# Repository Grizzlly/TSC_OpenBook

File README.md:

# OpenBook

An open source e-book reader based on ESP32.

## Block diagram

## Hardware features

The main component of the device is the `ESP32` microcontroller, which is responsible for all the processing and control of the device. The `ESP32` is a powerful microcontroller with built-in Wi-Fi and Bluetooth capabilities, making it ideal for IoT applications.

Apart from the microcontroller, we have:

- `E-Paper Display`: connected via SPI interface.
- `SD Card`: connected via SPI interface.
- `USB-C charging and protection`: connected to the battery and the microcontroller. It also has electro static discharge protection.
- `Environmental sensors`: connected via I2C interface. These sensors measure temperature, humidity, and pressure.

## Power consumption

The `ESP32` microcontroller consumes `~250 mA` when
in use.
The display uses `~15 mA` when active.
The environmental sensors use `~3 mA` when active.

In total when active, the device consumes `~270 mA`. Given
that the battery has a capacity of `1800 mAh`,
we should expect a battery life of `~6.5 hours` of continuous use.

## Pin mapping for the ESP32

| Pin Name | Description |                                                               
| -------- | ----------- |
| EN       | Reset |
| IO0      | Interrupt RTC |
| IO1      | Oscilator RTC |
| IO2      | SPI MISO |
| IO3      | Status display |
| IO4      | SD Card |
| IO5      | Data/Command |
| IO6      | SPI clock |
| IO7      | SPI data out |
| IO9      | Boot |
| IO10     | SPI E-Paper display command |
| IO11     | EPD |
| IO12     | Flash |
| IO13     | USB Data - |
| IO14     | USB Data + |
| IO15     | Navigation |
| IO16     | TX |
| IO17     | RX |
| IO18     | Reset DS3231 |
| IO19     | I2C Power |
| IO20     | EPD Power |
| IO21     | BME688 |
| IO22     | BME688 |
| IO23     | Reset display |

## BOM

| Piece Name                  | Quantity | Link                                                                                                                                                                                                               |
| --------------------------- | -------- | ------------------------------------------------------------------------------------------------------------------------------------------------------------------------------------------------------------------ |
| ADAFRUIT_LEDCHIP-LED0603    | 1        | https://www.snapeda.com/parts/KP-1608SURCK/Kingbright/view-part/?ref=search&t=LED%200603                                                                                                                           |
| C0402                       | 1        | https://componentsearchengine.com/part-view/CC0402MRX5R5BB106/YAGEO                                                                                                                                                |
| 112ATAARR03                 | 1        | https://www.snapeda.com/parts/112A-TAAR-R03/Attend/view-part/                                                                                                                                                      |
| 744043680                   | 1        | https://eu.mouser.com/ProductDetail/Wurth-Elektronik/744043680?qs=PGXP4M47uW6VkZq%252BkzjrHA%3D%3D                                                                                                                 |
| BD5229G-TR                  | 1        | https://www.snapeda.com/parts/BD5229G-TR/Rohm/view-part/?ref=search&t=BD5229G-TR                                                                                                                                   |
| CPH3225A                    | 1        | https://www.snapeda.com/parts/CPH3225A/Seiko/view-part/                                                                                                                                                            |
| BUTTON_CUSYOMV1             | 3        | https://www.snapeda.com/search/?q=EVQP7L01P&search-type=parts                                                                                                                                                      |
| DS3231SN                    | 1        | https://www.snapeda.com/parts/DS3231SN%23/Analog%20Devices/view-part/?ref=search&t=DS3231SN%23                                                                                                                     |
| ESP32                       | 1        | https://www.snapeda.com/parts/ESP32-C6-WROOM-1-N8/Espressif%20Systems/view-part/?ref=search&t=ESP32-C6-WROOM-1-N8                                                                                                  |
| VARISTOR                    | 1        | https://ro.mouser.com/ProductDetail/EPCOS-TDK/B72520T0350K062?qs=dEfas%2FXlABIszF52uu7vrg%3D%3D                                                                                                                    |
| SD0805S020S1R0              | 1        | https://componentsearchengine.com/part-view/SD0805S020S1R0/Kyocera%20AVX                                                                                                                                           |
| BME680                      | 1        | https://www.snapeda.com/parts/BME680/Bosch%20Sensortec/view-part/?ref=search&t=bme680                                                                                                                              |
| R0402                       | 1        | https://componentsearchengine.com/part-view/R0402%201%25%20100%20K%20(RC0402FR-07100KL)/YAGEO                                                                                                                      |
| MOSFET                      | 1        | https://componentsearchengine.com/part-view/DMG2305UX-7/Diodes%20Incorporated                                                                                                                                      |
| MCP73831                    | 1        | https://componentsearchengine.com/part-view/MCP73831T-2ACI%2FOT/Microchip                                                                                                                                          |
| SRJ                         | 1        | https://componentsearchengine.com/part-view/FH34SRJ-24S-0.5SH(99)/Hirose                                                                                                                                           |
| MBR0530                     | 1        | https://www.snapeda.com/parts/MBR0530/Onsemi/view-part/                                                                                                                                                            |
| PGB1010603MR                | 1        | https://www.snapeda.com/parts/PGB1010603MR/Littelfuse/view-part/                                                                                                                                                   |
| QWIIC_CONNECTOR             | 1        | https://www.snapeda.com/parts/PRT-14417/SparkFun/view-part/                                                                                                                                                        |
| RCL_CPOL-EU                 | 1        | https://grabcad.com/library/tantalum-smd-capacitor-type-b-3528-1                                                                                                                                                   |
| SAMACSYS_PARTS_USB4110-GF-A | 1        | https://www.snapeda.com/parts/USB4110-GF-A./Global%20Connector%20Technology/view-part/                                                                                                                             |
| SI1308EDL-T1-GE3            | 1        | https://www.snapeda.com/parts/SI1308EDL-T1-GE3/Vishay/view-part/                                                                                                                                                   |
| USBLC6-2SC6Y                | 1        | https://www.snapeda.com/parts/USBLC6-2SC6Y/STMicroelectronics/view-part/?ref=dk&t=USBLC6-2SC6Y&con_ref=None                                                                                                        |
| W25Q512JVEIQ                | 1        | https://www.snapeda.com/parts/W25Q512JVEIQ/Winbond%20Electronics/view-part/?ref=search&t=W25Q512JVEIQ                                                                                                              |
| XC6220A331MR-G              | 1        | https://ro.mouser.com/ProductDetail/Torex-Semiconductor/XC6220A331MR-G?qs=AsjdqWjXhJ8ZSWznL1J0gg%3D%3D&utm_source=octopart&utm_medium=aggregator&utm_campaign=865-XC6220A331MR-G&utm_content=Torex%20Semiconductor |

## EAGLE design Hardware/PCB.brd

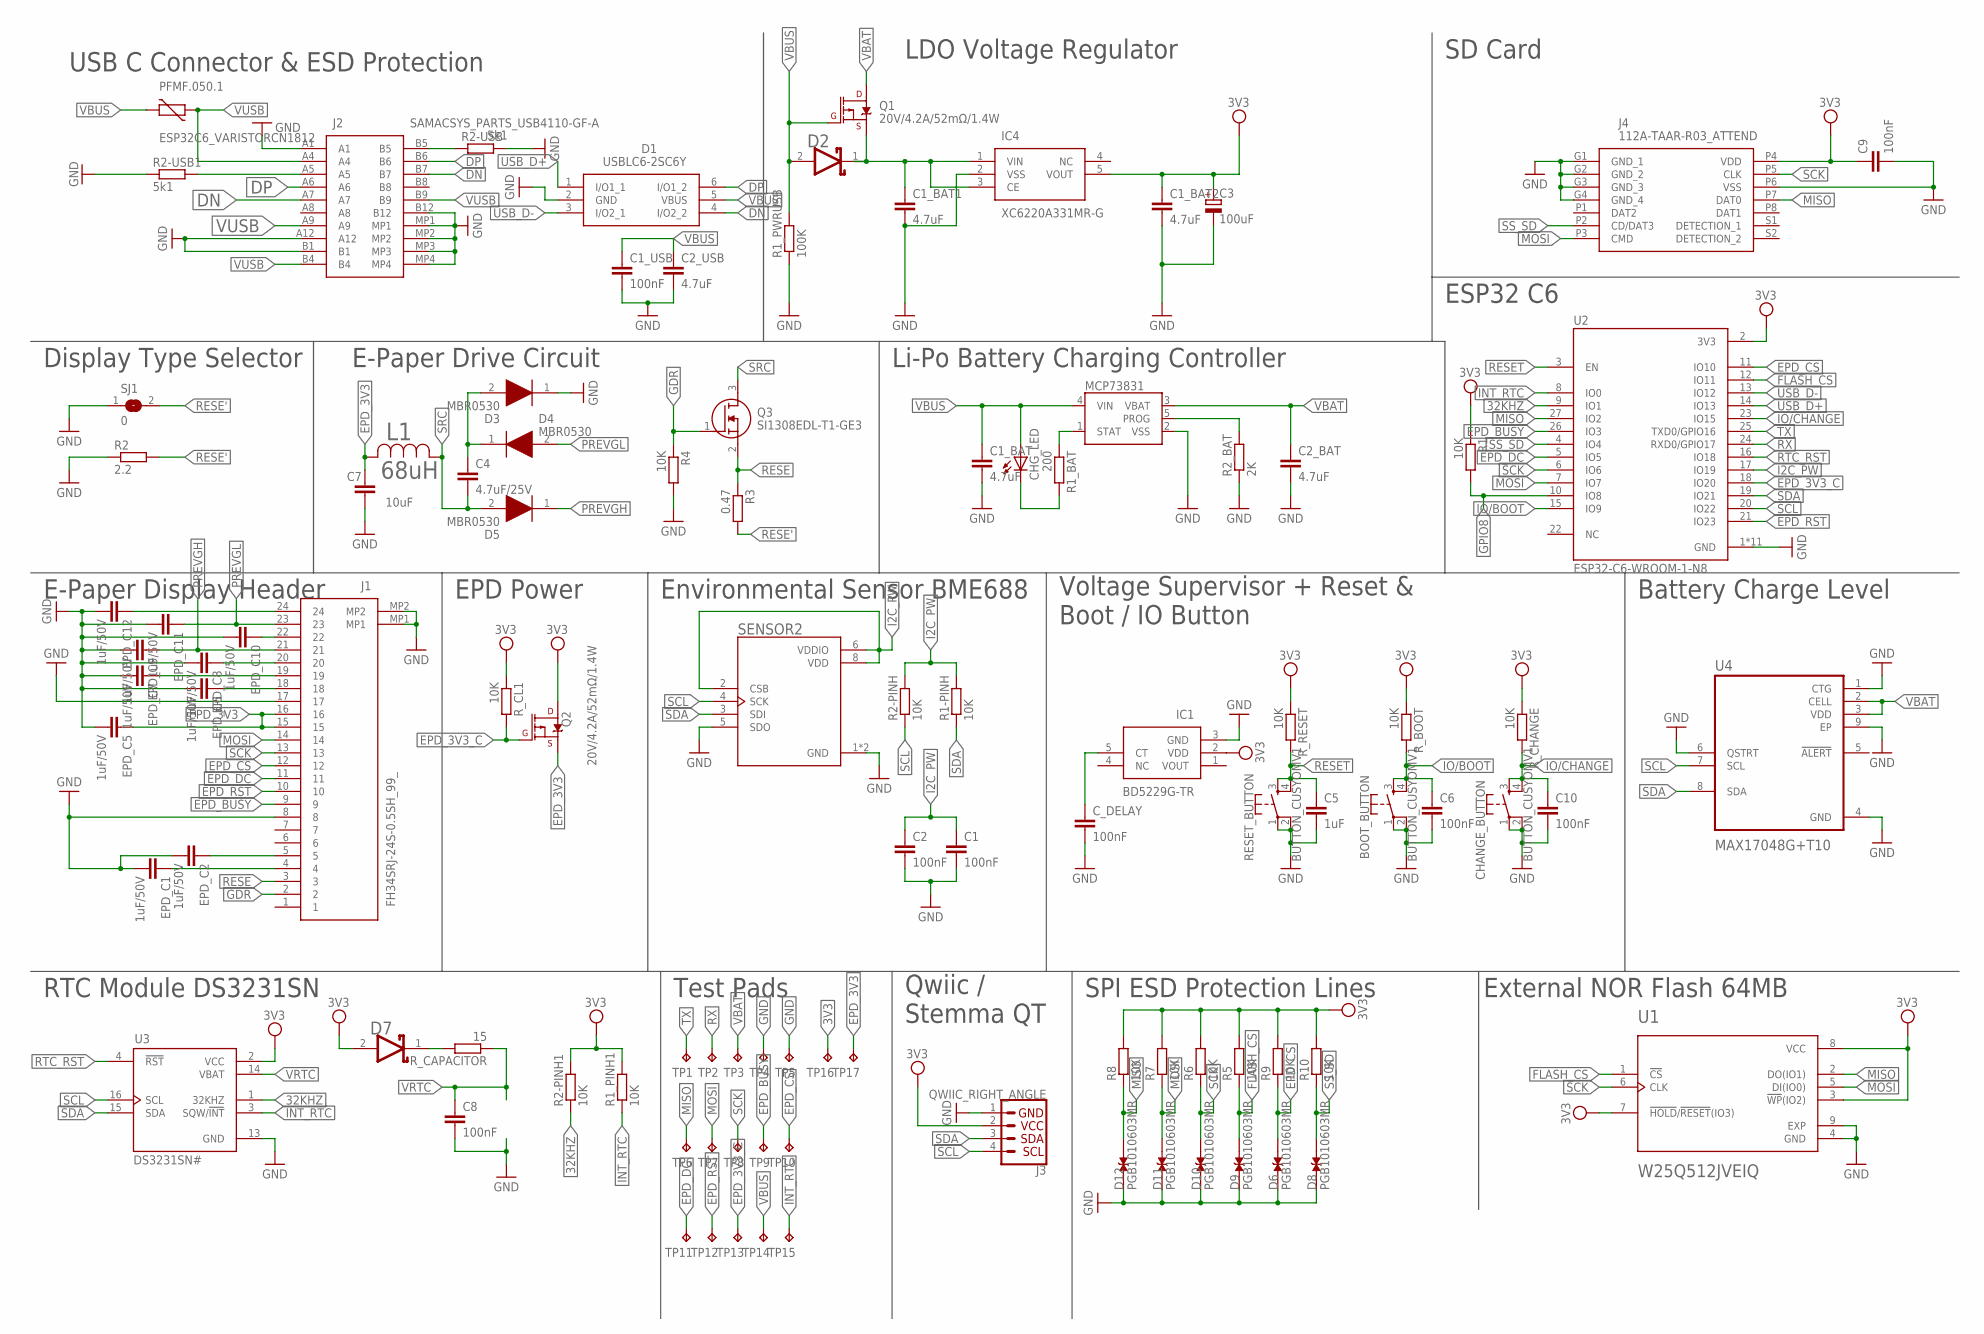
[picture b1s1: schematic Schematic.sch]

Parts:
BOOT_BUTTON: BUTTON_CUSYOMV1; MYBUTTON
C1, C1_USB, C2, C6, C8, C9, C10: 100nF; ESP32_WROVER_EAGLE-LTSPICE_C0402
C1_BAT, C1_BAT1, C1_BAT2, C2_BAT, C2_USB: 4.7uF; ESP32_WROVER_EAGLE-LTSPICE_C0402
C3: 100uF; RCL_CT3528
C4: 4.7uF/25V; ESP32_WROVER_EAGLE-LTSPICE_C0402
C5: 1uF; ESP32_WROVER_EAGLE-LTSPICE_C0402
C7: 10uF; ESP32_WROVER_EAGLE-LTSPICE_C0402
CHANGE_BUTTON: BUTTON_CUSYOMV1; MYBUTTON
CHG_LED: ADAFRUIT_LEDCHIP-LED0603; ADAFRUIT_CHIP-LED0603
C_DELAY: 100nF; ESP32_WROVER_EAGLE-LTSPICE_C0402
D1: USBLC6-2SC6Y; SOT95P280X145-6N
D2, D7: ESP32_WROVER_AVX---SD0805S020S1R0_AVX_SD0805S020S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; ESP32_WROVER_AVX---SD0805S020S1R0_AVX_SD0805S020S1R0_0
D3, D4, D5: MBR0530; SOD3716X135N
D6, D8, D9, D10, D11, D12: PGB1010603MR; DIOC1608X36N
EPD_C1, EPD_C2, EPD_C5, EPD_C6, EPD_C7, EPD_C8, EPD_C9, EPD_C10, EPD_C11, EPD_C12: 1uF/50V; ESP32_WROVER_EAGLE-LTSPICE_C0402
IC1: BD5229G-TR; SOT95P280X125-5N
IC4: XC6220A331MR-G; SOT95P280X120-5N
J1: FH34SRJ-24S-0.5SH_99_; FH34SRJ24S05SH99
J2: SAMACSYS_PARTS_USB4110-GF-A; SAMACSYS_PARTS_USB4110GFA
J3: QWIIC_RIGHT_ANGLE; JST04_1MM_RA
J4: 112A-TAAR-R03_ATTEND; 112ATAARR03ATTEND
L1: 68uH; IND_4828-WE-TPC_WRE
MCP73831: ESP32_WROVER_SPARKFUN-IC-POWER_MCP73831; ESP32_WROVER_SPARKFUN-IC-POWER_SOT23-5
PFMF.050.1: ESP32C6_VARISTORCN1812; ESP32C6_VARISTOR_CT/CN1812
Q1, Q2: 20V/4.2A/52mΩ/1.4W; ESP32_WROVER_SPARKFUN-DISCRETESEMI_SOT23-3
Q3: SI1308EDL-T1-GE3; SOT65P210X110-3N
R1, R1-PINH, R1_PINH1, R2-PINH, R2-PINH1, R4, R5, R6, R7, R8, R9, R10: 10K; ESP32_WROVER_EAGLE-LTSPICE_R0402
R1_BAT: 200; ESP32_WROVER_EAGLE-LTSPICE_R0402
R1_PWRUSB: 100K; ESP32_WROVER_EAGLE-LTSPICE_R0402
R2: 2.2; ESP32_WROVER_EAGLE-LTSPICE_R0402
R2-USB, R2-USB1: 5k1; ESP32_WROVER_EAGLE-LTSPICE_R0402
R2_BAT: 2K; ESP32_WROVER_EAGLE-LTSPICE_R0402
R3: 0.47; ESP32_WROVER_EAGLE-LTSPICE_R0402
RESET_BUTTON: BUTTON_CUSYOMV1; MYBUTTON
R_BOOT: 10K; ESP32_WROVER_EAGLE-LTSPICE_R0402
R_CAPACITOR: 15; ESP32_WROVER_EAGLE-LTSPICE_R0402
R_CHANGE: 10K; ESP32_WROVER_EAGLE-LTSPICE_R0402
R_CL1: 10K; ESP32_WROVER_EAGLE-LTSPICE_R0402
R_RESET: 10K; ESP32_WROVER_EAGLE-LTSPICE_R0402
SENSOR2: ESP32_WROVER_BME680_BME680; ESP32_WROVER_BME680_PSON80P300X300X100-8N
SJ1: 0; SJ
TP1, TP2, TP3, TP4, TP5, TP6, TP7, TP8, TP9, TP10, TP11, TP12, TP13, TP14, TP15, TP16, TP17: TPTP20R; TP20R
U1: W25Q512JVEIQ; SON127P600X800X80-9N
U2: ESP32-C6-WROOM-1-N8; XCVR_ESP32-C6-WROOM-1-N8
U3: DS3231SN#; SOIC127P1032X265-16N
U4: MAX17048G+T10; SON50P200X200X80-9N

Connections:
3V3: C1_BAT2.1, C3.+, C9.1, D7.2 (ANODE), IC1.2 (VDD), IC4.5 (VOUT), J3.2, J4.P4 (VDD), Q2.3 (D), R1.1, R1_PINH1.2, R2-PINH1.2, R5.2, R6.2, R7.2, R8.2, R9.2, R10.2, R_BOOT.1, R_CHANGE.1, R_CL1.1, R_RESET.1, TP16.TP, U1.3 (!WP!(IO2)), U1.7 (!HOLD!/!RESET!(IO3)), U1.8 (VCC), U2.2 (3V3), U3.2 (VCC)
32KHZ: R2-PINH1.1, U2.9 (IO1), U3.1 (32KHZ)
DN: D1.4 (I/O2_2), J2.A7, J2.B7
DP: D1.6 (I/O1_2), J2.A6, J2.B6
EPD_3V3: C7.1, EPD_C5.1, J1.15, J1.16, L1.2, Q2.2 (S), TP17.TP
EPD_3V3_C: Q2.1 (G), R_CL1.2, TP13.TP, U2.18 (IO20)
EPD_BUSY: J1.9, TP9.TP, U2.26 (IO3)
EPD_CS: D6.2, J1.12, R9.1, TP10.TP, U2.11 (IO10)
EPD_DC: J1.11, TP11.TP, U2.5 (IO5)
EPD_RST: J1.10, TP12.TP, U2.21 (IO23)
FLASH_CS: D9.2, R5.1, U1.1 (!CS), U2.12 (IO11)
GDR: J1.2, Q3.1 (G), R4.1
GND: BOOT_BUTTON.1, BOOT_BUTTON.2, C1.2, C1_BAT.2, C1_BAT1.2, C1_BAT2.2, C1_USB.2, C2.2, C2_BAT.2, C2_USB.2, C3.-, C5.2, C6.2, C7.2, C8.2, C9.2, C10.2, CHANGE_BUTTON.1, CHANGE_BUTTON.2, C_DELAY.2, D1.2 (GND), D3.1 (K), D6.1, D8.1, D9.1, D10.1, D11.1, D12.1, EPD_C1.2, EPD_C2.2, EPD_C5.2, EPD_C6.2, EPD_C7.2, EPD_C8.2, EPD_C9.2, EPD_C10.2, EPD_C11.2, EPD_C12.2, IC1.3 (GND), IC4.2 (VSS), J1.8, J1.17, J1.MP1, J1.MP2, J2.A1, J2.A12, J2.B1, J2.B12, J2.MP1, J2.MP2, J2.MP3, J2.MP4, J3.1, J4.G1 (GND_1), J4.G2 (GND_2), J4.G3 (GND_3), J4.G4 (GND_4), J4.P6 (VSS), MCP73831.2 (VSS), R1_PWRUSB.1, R2.1, R2-USB.2, R2-USB1.1, R2_BAT.1, R4.2, RESET_BUTTON.1, RESET_BUTTON.2, SENSOR2.1 (GND), SENSOR2.5 (SDO), SENSOR2.7 (GND), SJ1.1, TP4.TP, TP5.TP, U1.4 (GND), U1.9 (EXP), U2.1 (GND), U2.28 (GND), U2.29_1 (GND), U2.29_2 (GND), U2.29_3 (GND), U2.29_4 (GND), U2.29_5 (GND), U2.29_6 (GND), U2.29_7 (GND), U2.29_8 (GND), U2.29_9 (GND), U3.13 (GND), U4.1 (CTG), U4.4 (GND), U4.6 (QSTRT), U4.9 (EP)
GPIO8: R1.2, U2.10 (IO8)
I2C_PW: C1.1, C2.1, R1-PINH.2, R2-PINH.2, SENSOR2.2 (CSB), SENSOR2.6 (VDDIO), SENSOR2.8 (VDD), U2.17 (IO19)
INT_RTC: R1_PINH1.1, TP15.TP, U2.8 (IO0), U3.3 (SQW/!INT)
IO/BOOT: BOOT_BUTTON.3, BOOT_BUTTON.4, C6.1, R_BOOT.2, U2.15 (IO9)
IO/CHANGE: C10.1, CHANGE_BUTTON.3, CHANGE_BUTTON.4, R_CHANGE.2, U2.23 (IO15)
MISO: D12.2, J4.P7 (DAT0), R8.1, TP6.TP, U1.2 (DO(IO1)), U2.27 (IO2)
MOSI: D11.2, J1.14, J4.P3 (CMD), R7.1, TP7.TP, U1.5 (DI(IO0)), U2.7 (IO7)
unnamed: J2.A5, R2-USB1.2
unnamed: J2.B5, R2-USB.1
unnamed: C1_BAT1.1, D2.1 (CATHODE), IC4.1 (VIN), IC4.3 (CE), Q1.2 (S)
unnamed: C4.1, D3.2 (A), D4.1 (K)
unnamed: MCP73831.1 (STAT), R1_BAT.1
unnamed: CHG_LED.C, R1_BAT.2
unnamed: MCP73831.5 (PROG), R2_BAT.2
unnamed: EPD_C1.1, J1.4
unnamed: EPD_C2.1, J1.5
unnamed: EPD_C10.1, J1.22
unnamed: EPD_C8.1, J1.20
unnamed: EPD_C6.1, J1.18
unnamed: C_DELAY.1, IC1.5 (CT)
unnamed: EPD_C12.1, J1.24
unnamed: D7.1 (CATHODE), R_CAPACITOR.2
unnamed: EPD_C7.1, J1.19
PREVGH: D5.1 (K), EPD_C9.1, J1.21
PREVGL: D4.2 (A), EPD_C11.1, J1.23
RESE: J1.3, Q3.2 (S), R3.1
RESE': R2.2, R3.2, SJ1.2
RESET: C5.1, RESET_BUTTON.3, RESET_BUTTON.4, R_RESET.2, U2.3 (EN)
RTC_RST: U2.16 (IO18), U3.4 (!RST)
RX: TP2.TP, U2.24 (RXD0/GPIO17)
SCK: D10.2, J1.13, J4.P5 (CLK), R6.1, TP8.TP, U1.6 (CLK), U2.6 (IO6)
SCL: J3.4, R2-PINH.1, SENSOR2.4 (SCK), U2.20 (IO22), U3.16 (SCL), U4.7 (SCL)
SDA: J3.3, R1-PINH.1, SENSOR2.3 (SDI), U2.19 (IO21), U3.15 (SDA), U4.8 (SDA)
SRC: C4.2, D5.2 (A), L1.1, Q3.3 (D)
SS_SD: D8.2, J4.P2 (CD/DAT3), R10.1, U2.4 (IO4)
TX: TP1.TP, U2.25 (TXD0/GPIO16)
USB_D+: D1.1 (I/O1_1), U2.14 (IO13)
USB_D-: D1.3 (I/O2_1), U2.13 (IO12)
VBAT: C2_BAT.1, MCP73831.3 (VBAT), Q1.3 (D), TP3.TP, U4.2 (CELL), U4.3 (VDD)
VBUS: C1_BAT.1, C1_USB.1, C2_USB.1, CHG_LED.A, D1.5 (VBUS), D2.2 (ANODE), MCP73831.4 (VIN), PFMF.050.1.2, Q1.1 (G), R1_PWRUSB.2, TP14.TP
VRTC: C8.1, R_CAPACITOR.1, U3.14 (VBAT)
VUSB: J2.A4, J2.A9, J2.B4, J2.B9, PFMF.050.1.1

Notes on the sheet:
USB C Connector & ESD Protection
LDO Voltage Regulator
SD Card
Display Type Selector
E-Paper Drive Circuit
Li-Po Battery Charging Controller
ESP32 C6
E-Paper Display Header
EPD Power
Environmental Sensor BME688
Voltage Supervisor + Reset & Boot / IO Button
Battery Charge Level
RTC Module DS3231SN
Test Pads
Qwiic / Stemma QT
SPI ESD Protection Lines
External NOR Flash 64MB

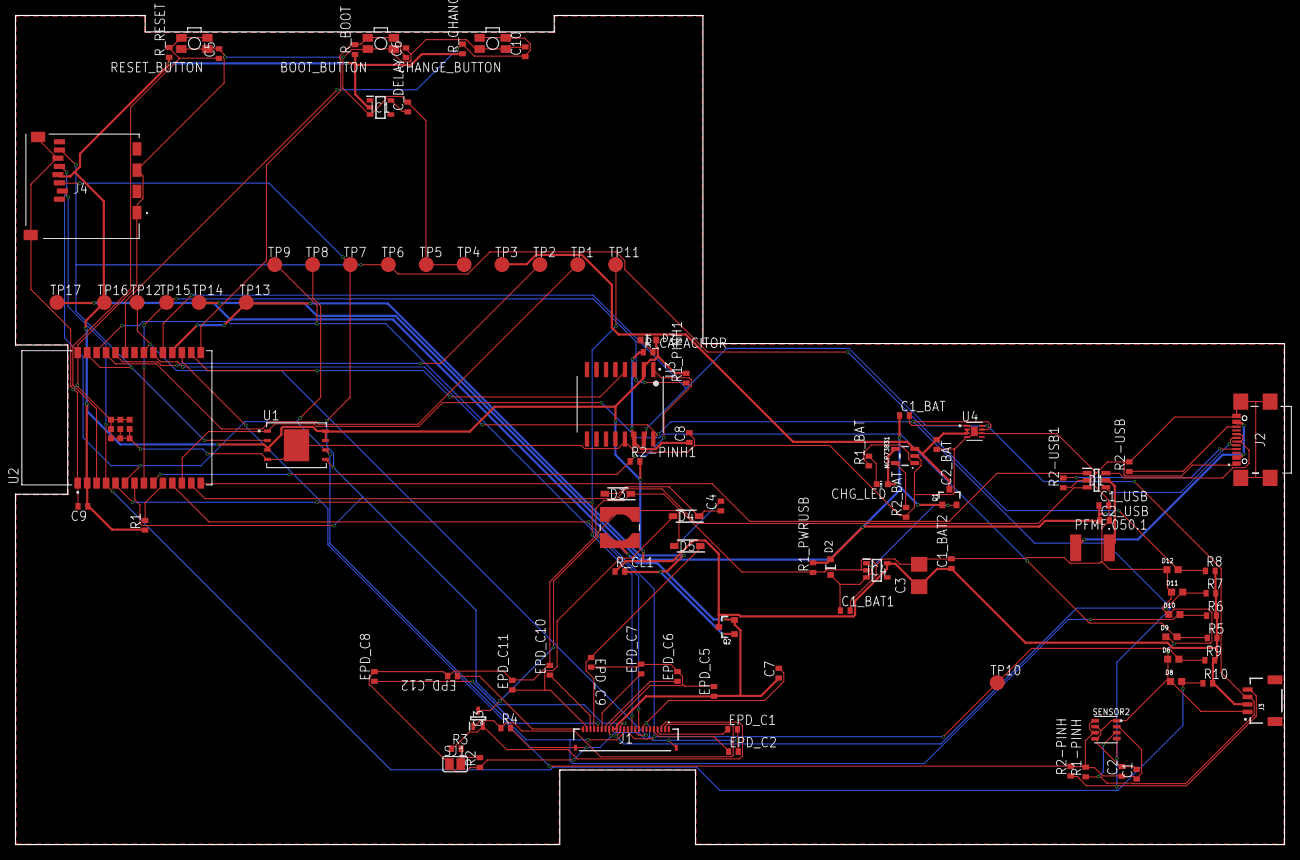
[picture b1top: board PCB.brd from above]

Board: 2 copper layers, 170.2 x 111.2 mm, 102 parts (0 on the bottom side), 55 nets.

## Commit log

2025-03-26 Added schematic.
2025-03-26 Create LICENSE
2025-04-05 Added PCB.
2025-04-05 Added gerbers.
2025-04-05 Added BOM.
2025-04-05 Added PNP.
2025-04-05 Added full device 3D model.
2025-04-05 Added 3D exploded view of device.
2025-04-05 Added renders.
2025-04-05 Added block diagram.
2025-04-05 README for device.
2025-04-11 Schematic fixes.
    Fixed some junctions not being properly connected.
    Added missing component values.
2025-04-11 Fixed PCB design.
    Fixed overlapping errors with L1 and via.
2025-04-12 Added pin mapping explanation for ESP32.

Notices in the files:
parts and their libraries:
COPYRIGHT: Copyright (C) 2024 Ultra Librarian. All rights reserved.
